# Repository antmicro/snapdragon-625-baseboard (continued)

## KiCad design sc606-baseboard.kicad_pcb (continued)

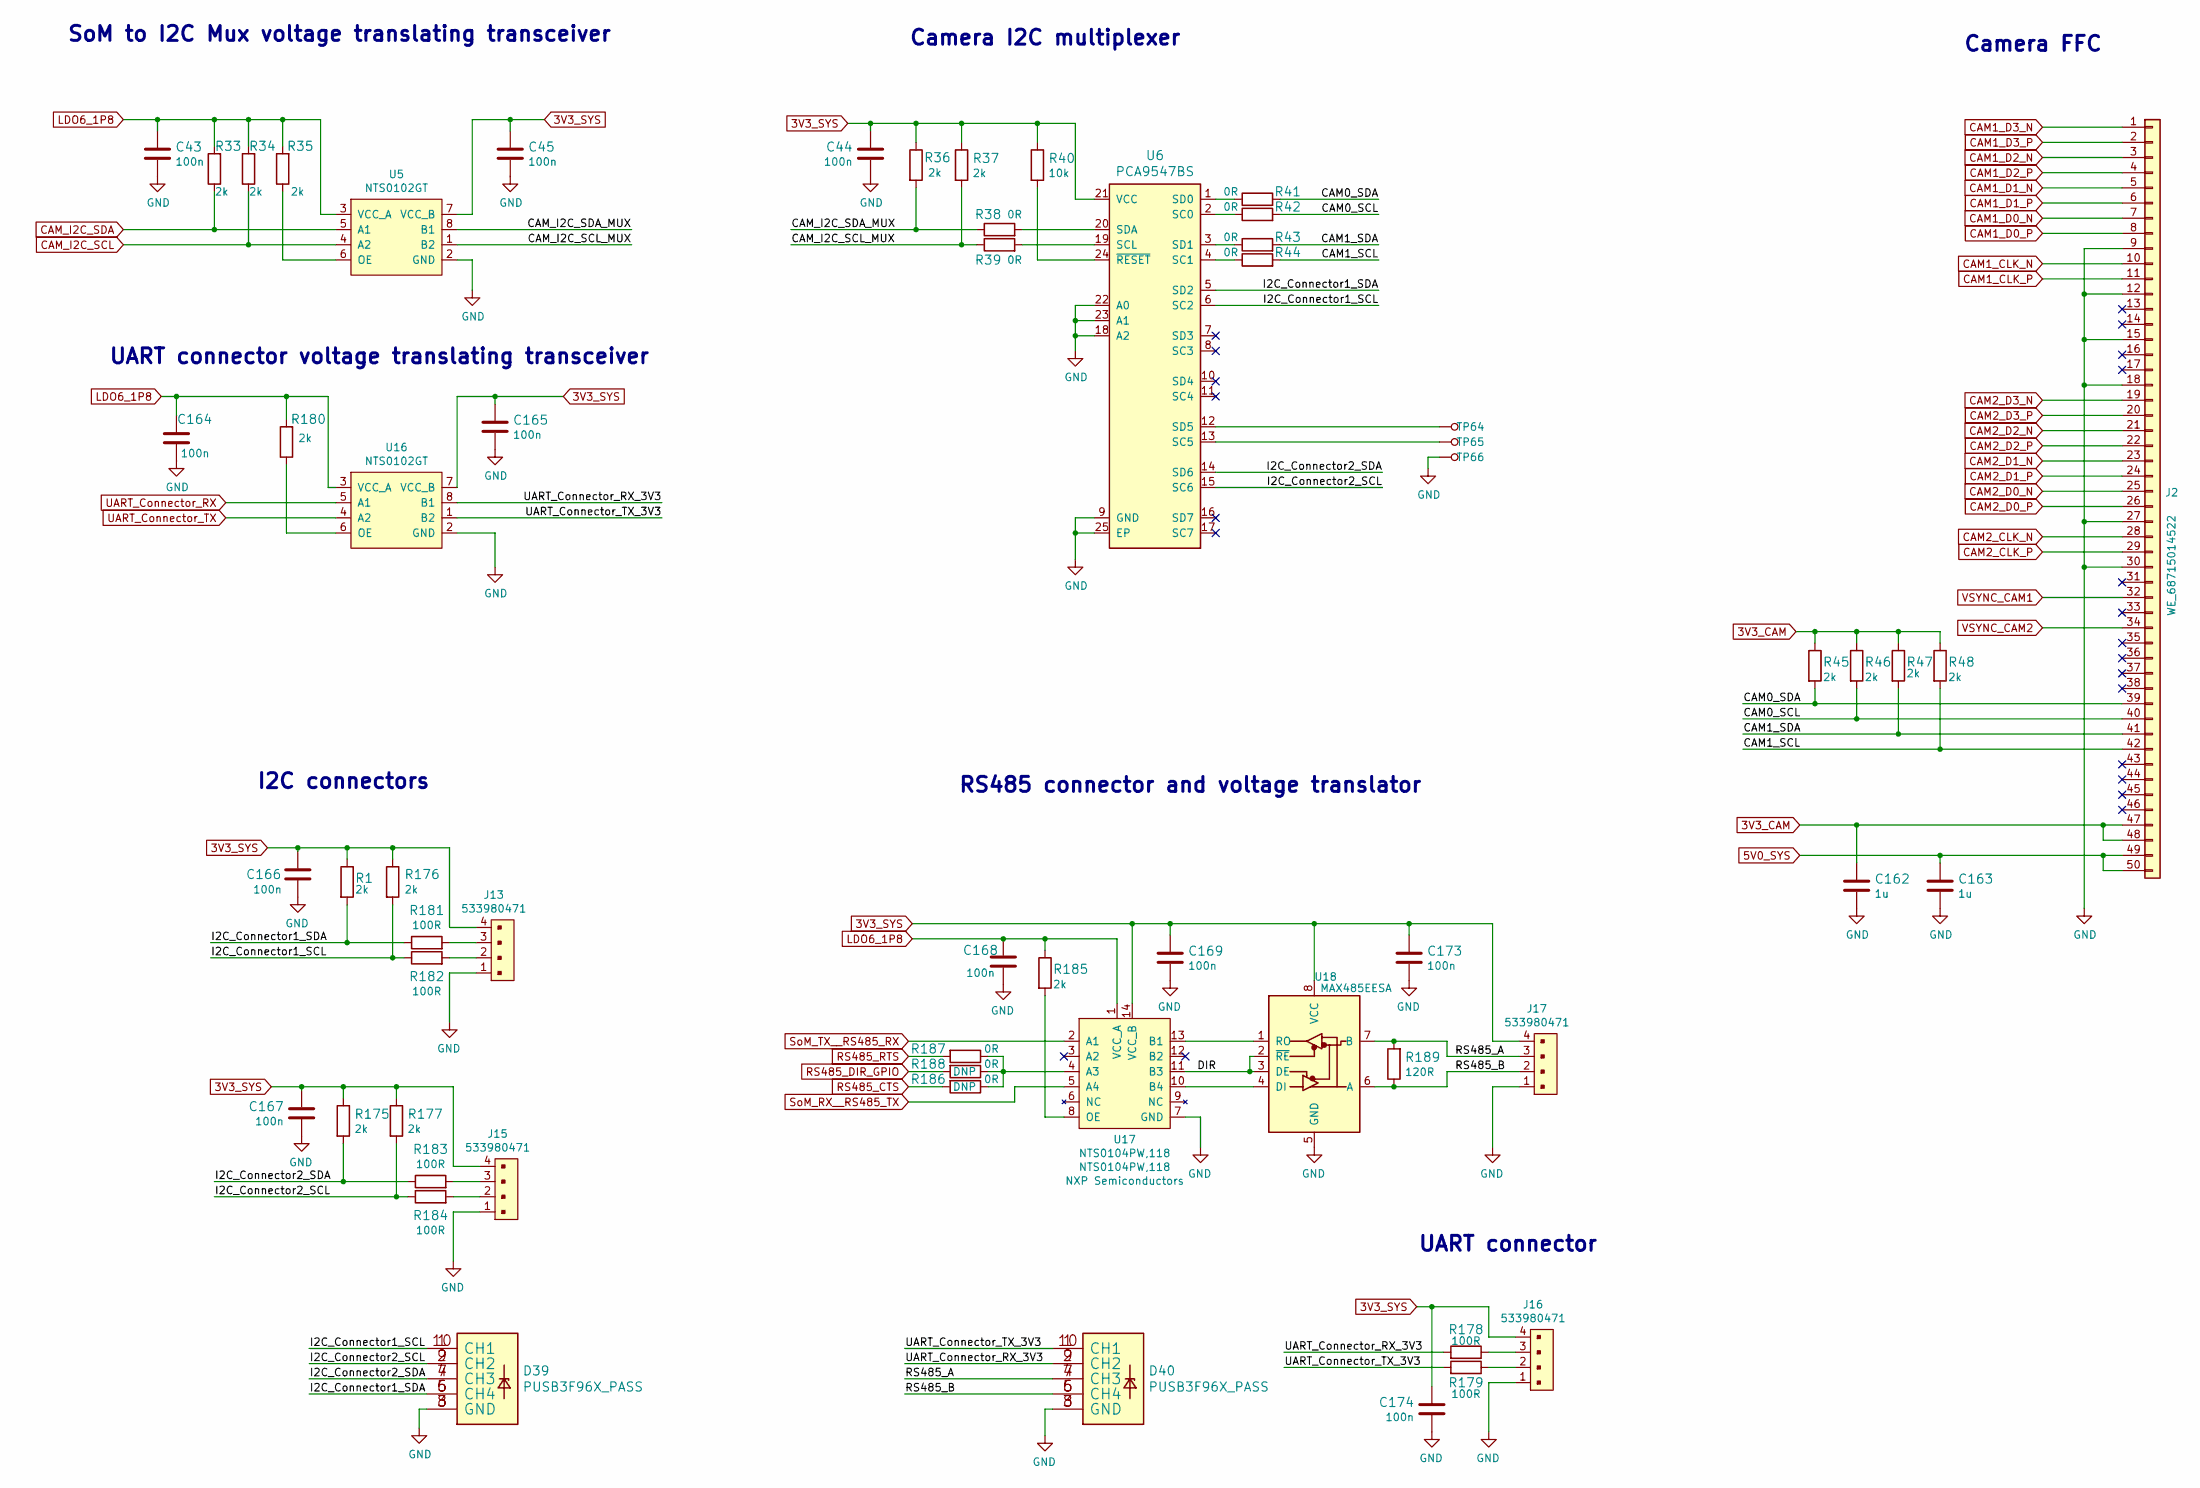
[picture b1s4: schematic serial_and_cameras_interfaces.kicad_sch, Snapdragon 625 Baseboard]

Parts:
C43, C45, C164, C165, C166, C167, C168, C169, C173, C174: C_100n_0402; 0402-cap; MPN GRM155R61H104KE14D
C44: C_100n_0402; 0402-cap; MPN 0402X104K6R3CT
C162, C163: C_1u_0402; 0402-cap; MPN C1005X6S1A105K050BC
D39, D40: PUSB3F96X_PASS; PUSB3F96X; MPN PUSB3F96X
J2: WE_68715014522; MPN 68715014522
J13, J15, J16, J17: 533980471; Molex_PicoBlade_53398-0471_1x04-1MP_P1.25mm_Vertical; MPN 0533980471
R1, R33, R34, R35, R36, R37, R45, R46, R47, R48, R175, R176, R177, R180, R185: R_2k_0402; 0402-res; MPN CRCW04022K00FKED
R38, R39, R41, R42, R43, R44, R186, R187, R188: R_0R_0402; 0402-res; MPN ERJ2GE0R00X
R40: R_10k_0402; 0402-res; MPN CRCW040210K0FKEDHP
R178, R179, R181, R182, R183, R184: R_100R_0402; 0402-res; MPN CR0402-FX-1000GLF
R189: R_120R_0603; 0603-res; MPN CRCW0603120RFKEA
TP64, TP65, TP66: TP_SMD_1_5MM; TP-R-1.5
U5, U16: NTS0102GT; PSON50P100X195X50-8N; MPN NTS0102GT
U6: PCA9547BS; HVQFN24; MPN PCA9547BS,118
U17: NTS0104PW,118; TSSOP-14_W4.4mm; MPN NTS0104PW,118
U18: MAX485EESA; SOIC-8_W3.9mm; MPN MAX485EESA

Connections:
3V3_CAM: C162.1, J2.47, J2.48, R45.1, R46.1, R47.1, R48.1; also elsewhere on the board
3V3_SYS: C44.1, C45.1, C165.1, C166.1, C167.1, C169.1, C173.1, C174.1, J13.4, J15.4, J16.4, J17.4, R1.1, R36.1, R37.1, R40.1, R175.1, R176.1, R177.1, U5.7 (VCC_B), U6.21 (VCC), U16.7 (VCC_B), U17.14 (VCC_B), U18.8 (VCC); also elsewhere on the board
5V0_SYS: C163.1, J2.49, J2.50; also elsewhere on the board
/serial_and_cameras_interfaces/CAM0_SCL: J2.40, R42.2, R46.2
/serial_and_cameras_interfaces/CAM0_SDA: J2.39, R41.2, R45.2
/serial_and_cameras_interfaces/CAM1_SCL: J2.42, R44.2, R48.2
/serial_and_cameras_interfaces/CAM1_SDA: J2.41, R43.2, R47.2
/serial_and_cameras_interfaces/CAM_I2C_SCL_MUX: R37.2, R39.1, U5.1 (B2)
/serial_and_cameras_interfaces/CAM_I2C_SDA_MUX: R36.2, R38.1, U5.8 (B1)
/serial_and_cameras_interfaces/DIR: U17.11 (B3), U18.2 (~RE), U18.3 (DE)
/serial_and_cameras_interfaces/I2C_Connector1_SCL: D39.1 (CH1), D39.10 (CH1), R176.2, R182.1, U6.6 (SC2)
/serial_and_cameras_interfaces/I2C_Connector1_SDA: D39.5 (CH4), D39.6 (CH4), R1.2, R181.1, U6.5 (SD2)
/serial_and_cameras_interfaces/I2C_Connector2_SCL: D39.2 (CH2), D39.9 (CH2), R177.2, R184.1, U6.15 (SC6)
/serial_and_cameras_interfaces/I2C_Connector2_SDA: D39.4 (CH3), D39.7 (CH3), R175.2, R183.1, U6.14 (SD6)
/serial_and_cameras_interfaces/RS485_A: D40.4 (CH3), D40.7 (CH3), J17.3, R189.2, U18.7 (B)
/serial_and_cameras_interfaces/RS485_B: D40.5 (CH4), D40.6 (CH4), J17.2, R189.1, U18.6 (A)
/serial_and_cameras_interfaces/UART_Connector_RX_3V3: D40.2 (CH2), D40.9 (CH2), R178.2, U16.8 (B1)
/serial_and_cameras_interfaces/UART_Connector_TX_3V3: D40.1 (CH1), D40.10 (CH1), R179.2, U16.1 (B2)
CAM1_CLK_N: J2.10; also elsewhere on the board
CAM1_CLK_P: J2.11; also elsewhere on the board
CAM1_D0_N: J2.7; also elsewhere on the board
CAM1_D0_P: J2.8; also elsewhere on the board
CAM1_D1_N: J2.5; also elsewhere on the board
CAM1_D1_P: J2.6; also elsewhere on the board
CAM1_D2_N: J2.3; also elsewhere on the board
CAM1_D2_P: J2.4; also elsewhere on the board
CAM1_D3_N: J2.1; also elsewhere on the board
CAM1_D3_P: J2.2; also elsewhere on the board
CAM2_CLK_N: J2.28; also elsewhere on the board
CAM2_CLK_P: J2.29; also elsewhere on the board
CAM2_D0_N: J2.25; also elsewhere on the board
CAM2_D0_P: J2.26; also elsewhere on the board
CAM2_D1_N: J2.23; also elsewhere on the board
CAM2_D1_P: J2.24; also elsewhere on the board
CAM2_D2_N: J2.21; also elsewhere on the board
CAM2_D2_P: J2.22; also elsewhere on the board
CAM2_D3_N: J2.19; also elsewhere on the board
CAM2_D3_P: J2.20; also elsewhere on the board
CAM_I2C_SCL: R34.1, U5.4 (A2); also elsewhere on the board
CAM_I2C_SDA: R33.1, U5.5 (A1); also elsewhere on the board
GND: C43.2, C44.2, C45.2, C162.2, C163.2, C164.2, C165.2, C166.2, C167.2, C168.2, C169.2, C173.2, C174.2, D39.3 (GND), D39.8 (GND), D40.3 (GND), D40.8 (GND), J2.9, J2.12, J2.15, J2.18, J2.27, J2.30, J13.1, J15.1, J16.1, J17.1, TP66.1, U5.2 (GND), U6.9 (GND), U6.18 (A2), U6.22 (A0), U6.23 (A1), U6.25 (EP), U16.2 (GND), U17.7 (GND), U18.5 (GND); also elsewhere on the board
LDO6_1P8: C43.1, C164.1, C168.1, R33.2, R34.2, R35.2, R180.2, R185.1, U5.3 (VCC_A), U16.3 (VCC_A), U17.1 (VCC_A); also elsewhere on the board
unnamed: J13.2, R182.2
unnamed: J13.3, R181.2
unnamed: J15.2, R184.2
unnamed: J15.3, R183.2
unnamed: J16.2, R179.1
unnamed: J16.3, R178.1
unnamed: R35.1, U5.6 (OE)
unnamed: R38.2, U6.20 (SDA)
unnamed: R39.2, U6.19 (SCL)
unnamed: R40.2, U6.24 (~RESET)
unnamed: R41.1, U6.1 (SD0)
unnamed: R42.1, U6.2 (SC0)
unnamed: R43.1, U6.3 (SD1)
unnamed: R44.1, U6.4 (SC1)
unnamed: R180.1, U16.6 (OE)
unnamed: R185.2, U17.8 (OE)
unnamed: R186.1, R187.1, R188.1, U17.4 (A3)
unnamed: TP64.1, U6.12 (SD5)
unnamed: TP65.1, U6.13 (SC5)
unnamed: U17.10 (B4), U18.4 (DI)
unnamed: U17.13 (B1), U18.1 (RO)
RS485_CTS: R186.2; also elsewhere on the board
RS485_DIR_GPIO: R188.2; also elsewhere on the board
RS485_RTS: R187.2; also elsewhere on the board
SoM_RX__RS485_TX: U17.5 (A4); also elsewhere on the board
SoM_TX__RS485_RX: U17.2 (A1); also elsewhere on the board
UART_Connector_RX: U16.5 (A1); also elsewhere on the board
UART_Connector_TX: U16.4 (A2); also elsewhere on the board
VSYNC_CAM1: J2.32; also elsewhere on the board
VSYNC_CAM2: J2.34; also elsewhere on the board

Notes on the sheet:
UART connector
UART connector voltage translating transceiver
RS485 connector and voltage translator
SoM to I2C Mux voltage translating transceiver
Camera I2C multiplexer
Camera FFC
I2C connectors

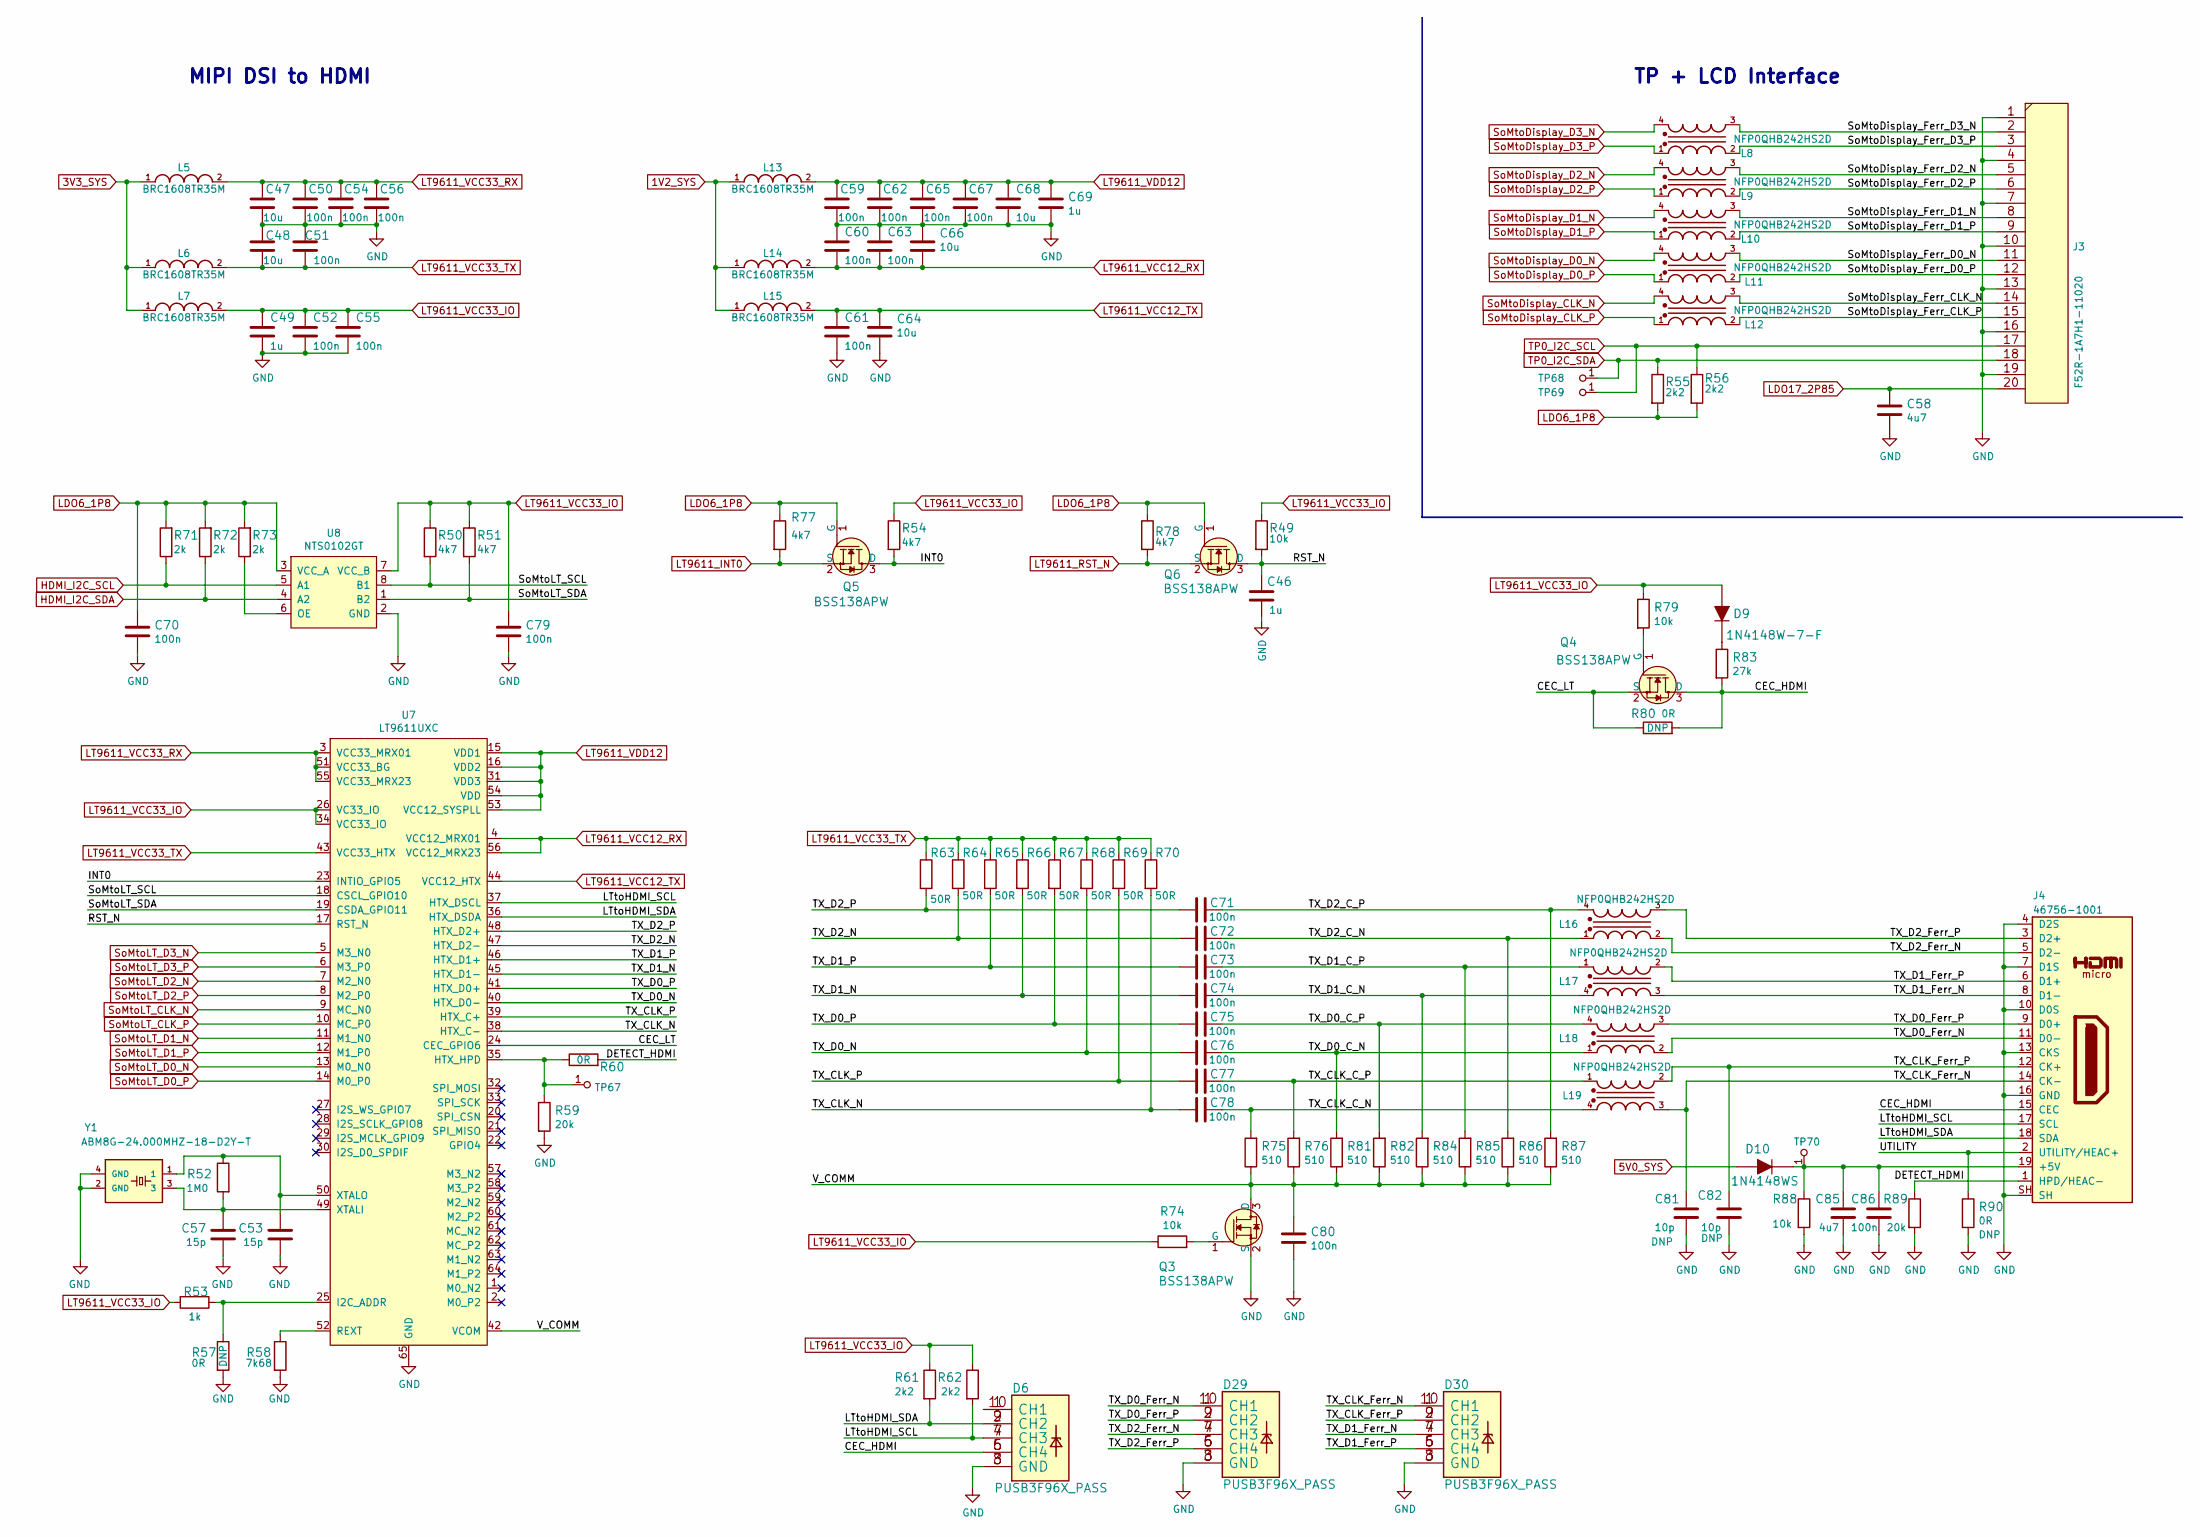
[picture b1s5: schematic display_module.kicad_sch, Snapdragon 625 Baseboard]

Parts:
C46, C49, C69: C_1u_0402; 0402-cap; MPN C1005X6S1A105K050BC
C47, C48, C64, C66, C68: C_10u_0402; 0402-cap; MPN CC0402MRX5R5BB106
C50, C51, C52, C54, C55, C56, C59, C60, C61, C62, C63, C65, C67, C70, C71, C72, C73, C74, C75, C76, C77, C78, C79, C80, C86: C_100n_0402; 0402-cap; MPN GRM155R61H104KE14D
C53, C57: C_15p_0402; 0402-cap; MPN MC0402N150J500CT
C58, C85: C_4u7_0402; 0402-cap; MPN GRM155R61A475MEAAD
C81, C82: C_10p_0402; 0402-cap; MPN MC0402N100D500CT
D6, D29, D30: PUSB3F96X_PASS; PUSB3F96X; MPN PUSB3F96X
D9: 1N4148W-7-F; SOD-123; MPN 1N4148W-7-F
D10: 1N4148WS; SOD-323F; MPN 1N4148WS
J3: F52R-1A7H1-11020; MPN F52R-1A7H1-11020
J4: 46756-1001; HDMI_Micro-D_Molex_46765-1x01; MPN 467651001
L5, L6, L7, L13, L14, L15: BRC1608TR35M; INDC1608X100N; MPN BRC1608TR35M
L8, L9, L10, L11, L12, L16, L17, L18, L19: NFP0QHB242HS2D; FIL_NFP0QHB242HS2D; MPN NFP0QHB242HS2D
Q3, Q4, Q5, Q6: BSS138APW; SC70-3; MPN BSS138PW
R49, R74, R79, R88: R_10k_0402; 0402-res; MPN CRCW040210K0FKEDHP
R50, R51, R54, R77, R78: R_4k7_0402; 0402-res; MPN MCS04020C4701FE000
R52: R_1M0_0402; 0402-res; MPN CRG0402F1M0
R53: R_1k_0402; 0402-res; MPN CR0402-FX-1001GLF
R55, R56, R61, R62: R_2k2_0402; 0402-res; MPN RC0402FR-072K2L
R57, R60, R80, R90: R_0R_0402; 0402-res; MPN ERJ2GE0R00X
R58: R_7k68_0603; 0603-res; MPN WR06X7681FTL
R59, R89: R_20k_0402; 0402-res; MPN CRCW040220K0FKED
R63, R64, R65, R66, R67, R68, R69, R70: R_50R_0402; 0402-res; MPN RN73R1ETTP50R0F50
R71, R72, R73: R_2k_0402; 0402-res; MPN CRCW04022K00FKED
R75, R76, R81, R82, R84, R85, R86, R87: R_510_0402; 0402-res; MPN CRCW0402510RFKEDC
R83: R_27k_0402; 0402-res; MPN ERJ2RKF2702X
TP67, TP68, TP69, TP70: TP; TP-R-1.5
U7: LT9611UXC; LT9611; MPN LT9611
U8: NTS0102GT; PSON50P100X195X50-8N; MPN NTS0102GT
Y1: ABM8G-24.000MHZ-18-D2Y-T; KX-7; MPN ABM8G-24.000MHZ-18-D2Y-T

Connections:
1V2_SYS: L13.1, L14.1, L15.1; also elsewhere on the board
3V3_SYS: L5.1, L6.1, L7.1; also elsewhere on the board
5V0_SYS: D10.A; also elsewhere on the board
/display module/CEC_HDMI: D6.5 (CH4), D6.6 (CH4), J4.15 (CEC), Q4.3 (D), R80.2, R83.2
/display module/CEC_LT: Q4.2 (S), R80.1, U7.24 (CEC_GPIO6)
/display module/DETECT_HDMI: J4.1 (HPD/HEAC-), R60.2, R89.1
/display module/INT0: Q5.3 (D), R54.2, U7.23 (INTIO_GPIO5)
/display module/LTtoHDMI_SCL: D6.4 (CH3), D6.7 (CH3), J4.17 (SCL), R62.2, U7.37 (HTX_DSCL)
/display module/LTtoHDMI_SDA: D6.2 (CH2), D6.9 (CH2), J4.18 (SDA), R61.2, U7.36 (HTX_DSDA)
/display module/RST_N: C46.1, Q6.3 (D), R49.2, U7.17 (RST_N)
/display module/SoMtoDisplay_Ferr_CLK_N: J3.14, L12.3
/display module/SoMtoDisplay_Ferr_CLK_P: J3.15, L12.2
/display module/SoMtoDisplay_Ferr_D0_N: J3.11, L11.3
/display module/SoMtoDisplay_Ferr_D0_P: J3.12, L11.2
/display module/SoMtoDisplay_Ferr_D1_N: J3.8, L10.3
/display module/SoMtoDisplay_Ferr_D1_P: J3.9, L10.2
/display module/SoMtoDisplay_Ferr_D2_N: J3.5, L9.3
/display module/SoMtoDisplay_Ferr_D2_P: J3.6, L9.2
/display module/SoMtoDisplay_Ferr_D3_N: J3.2, L8.3
/display module/SoMtoDisplay_Ferr_D3_P: J3.3, L8.2
/display module/SoMtoLT_SCL: R50.2, U7.18 (CSCL_GPIO10), U8.8 (B1)
/display module/SoMtoLT_SDA: R51.2, U7.19 (CSDA_GPIO11), U8.1 (B2)
/display module/TX_CLK_C_N: C78.1, L19.4, R75.2
/display module/TX_CLK_C_P: C77.1, L19.1, R76.2
/display module/TX_CLK_Ferr_N: C81.1, D30.1 (CH1), D30.10 (CH1), J4.14 (CK-), L19.3
/display module/TX_CLK_Ferr_P: C82.1, D30.2 (CH2), D30.9 (CH2), J4.12 (CK+), L19.2
/display module/TX_CLK_N: C78.2, R70.2, U7.38 (HTX_C-)
/display module/TX_CLK_P: C77.2, R69.2, U7.39 (HTX_C+)
/display module/TX_D0_C_N: C76.1, L18.1, R81.2
/display module/TX_D0_C_P: C75.1, L18.4, R82.2
/display module/TX_D0_Ferr_N: D29.1 (CH1), D29.10 (CH1), J4.11 (D0-), L18.2
/display module/TX_D0_Ferr_P: D29.2 (CH2), D29.9 (CH2), J4.9 (D0+), L18.3
/display module/TX_D0_N: C76.2, R68.2, U7.40 (HTX_D0-)
/display module/TX_D0_P: C75.2, R67.2, U7.41 (HTX_D0+)
/display module/TX_D1_C_N: C74.1, L17.4, R84.2
/display module/TX_D1_C_P: C73.1, L17.1, R85.2
/display module/TX_D1_Ferr_N: D30.4 (CH3), D30.7 (CH3), J4.8 (D1-), L17.3
/display module/TX_D1_Ferr_P: D30.5 (CH4), D30.6 (CH4), J4.6 (D1+), L17.2
/display module/TX_D1_N: C74.2, R66.2, U7.45 (HTX_D1-)
/display module/TX_D1_P: C73.2, R65.2, U7.46 (HTX_D1+)
/display module/TX_D2_C_N: C72.1, L16.1, R86.2
/display module/TX_D2_C_P: C71.1, L16.4, R87.2
/display module/TX_D2_Ferr_N: D29.4 (CH3), D29.7 (CH3), J4.5 (D2-), L16.2
/display module/TX_D2_Ferr_P: D29.5 (CH4), D29.6 (CH4), J4.3 (D2+), L16.3
/display module/TX_D2_N: C72.2, R64.2, U7.47 (HTX_D2-)
/display module/TX_D2_P: C71.2, R63.2, U7.48 (HTX_D2+)
/display module/UTILITY: J4.2 (UTILITY/HEAC+), R90.1
/display module/V_COMM: C80.1, Q3.3 (D), R75.1, R76.1, R81.1, R82.1, R84.1, R85.1, R86.1, R87.1, U7.42 (VCOM)
GND: C46.2, C47.1, C48.2, C49.2, C50.1, C51.2, C52.2, C53.2, C54.1, C55.2, C56.1, C57.2, C58.2, C59.1, C60.1, C61.2, C62.1, C63.1, C64.2, C65.1, C66.1, C67.1, C68.2, C69.2, C70.2, C79.2, C80.2, C81.2, C82.2, C85.2, C86.2, D6.3 (GND), D6.8 (GND), D29.3 (GND), D29.8 (GND), D30.3 (GND), D30.8 (GND), J3.1, J3.4, J3.7, J3.10, J3.13, J3.16, J3.19, J4.4 (D2S), J4.7 (D1S), J4.10 (D0S), J4.13 (CKS), J4.16 (GND), J4.SH, Q3.2 (S), R57.2, R58.2, R59.2, R88.2, R89.2, R90.2, U7.65 (GND), U8.2 (GND), Y1.2 (GND), Y1.4 (GND); also elsewhere on the board
HDMI_I2C_SCL: R71.1, U8.5 (A1); also elsewhere on the board
HDMI_I2C_SDA: R72.1, U8.4 (A2); also elsewhere on the board
LDO6_1P8: C70.1, Q5.1 (G), Q6.1 (G), R55.2, R56.2, R71.2, R72.2, R73.2, R77.1, R78.1, U8.3 (VCC_A); also elsewhere on the board
LDO17_2P85: C58.1, J3.20; also elsewhere on the board
LT9611_INT0: Q5.2 (S), R77.2; also elsewhere on the board
LT9611_RST_N: Q6.2 (S), R78.2; also elsewhere on the board
LT9611_VCC12_RX: C60.2, C63.2, C66.2, L14.2, U7.4 (VCC12_MRX01), U7.56 (VCC12_MRX23)
LT9611_VCC12_TX: C61.1, C64.1, L15.2, U7.44 (VCC12_HTX)
LT9611_VCC33_IO: C49.1, C52.1, C55.1, C79.1, D9.A, L7.2, R49.1, R50.1, R51.1, R53.2, R54.1, R61.1, R62.1, R74.1, R79.1, U7.26 (VC33_IO), U7.34 (VCC33_IO), U8.7 (VCC_B)
LT9611_VCC33_RX: C47.2, C50.2, C54.2, C56.2, L5.2, U7.3 (VCC33_MRX01), U7.51 (VCC33_BG), U7.55 (VCC33_MRX23)
LT9611_VCC33_TX: C48.1, C51.1, L6.2, R63.1, R64.1, R65.1, R66.1, R67.1, R68.1, R69.1, R70.1, U7.43 (VCC33_HTX)
LT9611_VDD12: C59.2, C62.2, C65.2, C67.2, C68.1, C69.1, L13.2, U7.15 (VDD1), U7.16 (VDD2), U7.31 (VDD3), U7.53 (VCC12_SYSPLL), U7.54 (VDD)
unnamed: C53.1, R52.1, U7.50 (XTALO), Y1.1
unnamed: C57.1, R52.2, U7.49 (XTALI), Y1.3
unnamed: C85.1, C86.1, D10.K, J4.19 (+5V), R88.1, TP70.1
unnamed: D6.1 (CH1), D6.10 (CH1)
unnamed: D9.K, R83.1
unnamed: Q3.1 (G), R74.2
unnamed: Q4.1 (G), R79.2
unnamed: R53.1, R57.1, U7.25 (I2C_ADDR)
unnamed: R58.1, U7.52 (REXT)
unnamed: R59.1, R60.1, TP67.1, U7.35 (HTX_HPD)
unnamed: R73.1, U8.6 (OE)
SoMtoDisplay_CLK_N: L12.4; also elsewhere on the board
SoMtoDisplay_CLK_P: L12.1; also elsewhere on the board
SoMtoDisplay_D0_N: L11.4; also elsewhere on the board
SoMtoDisplay_D0_P: L11.1; also elsewhere on the board
SoMtoDisplay_D1_N: L10.4; also elsewhere on the board
SoMtoDisplay_D1_P: L10.1; also elsewhere on the board
SoMtoDisplay_D2_N: L9.4; also elsewhere on the board
SoMtoDisplay_D2_P: L9.1; also elsewhere on the board
SoMtoDisplay_D3_N: L8.4; also elsewhere on the board
SoMtoDisplay_D3_P: L8.1; also elsewhere on the board
SoMtoLT_CLK_N: U7.9 (MC_N0); also elsewhere on the board
SoMtoLT_CLK_P: U7.10 (MC_P0); also elsewhere on the board
SoMtoLT_D0_N: U7.13 (M0_N0); also elsewhere on the board
SoMtoLT_D0_P: U7.14 (M0_P0); also elsewhere on the board
SoMtoLT_D1_N: U7.11 (M1_N0); also elsewhere on the board
SoMtoLT_D1_P: U7.12 (M1_P0); also elsewhere on the board
SoMtoLT_D2_N: U7.7 (M2_N0); also elsewhere on the board
SoMtoLT_D2_P: U7.8 (M2_P0); also elsewhere on the board
SoMtoLT_D3_N: U7.5 (M3_N0); also elsewhere on the board
SoMtoLT_D3_P: U7.6 (M3_P0); also elsewhere on the board
TP0_I2C_SCL: J3.17, R56.1, TP69.1; also elsewhere on the board
TP0_I2C_SDA: J3.18, R55.1, TP68.1; also elsewhere on the board

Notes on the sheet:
MIPI DSI to HDMI
TP + LCD Interface

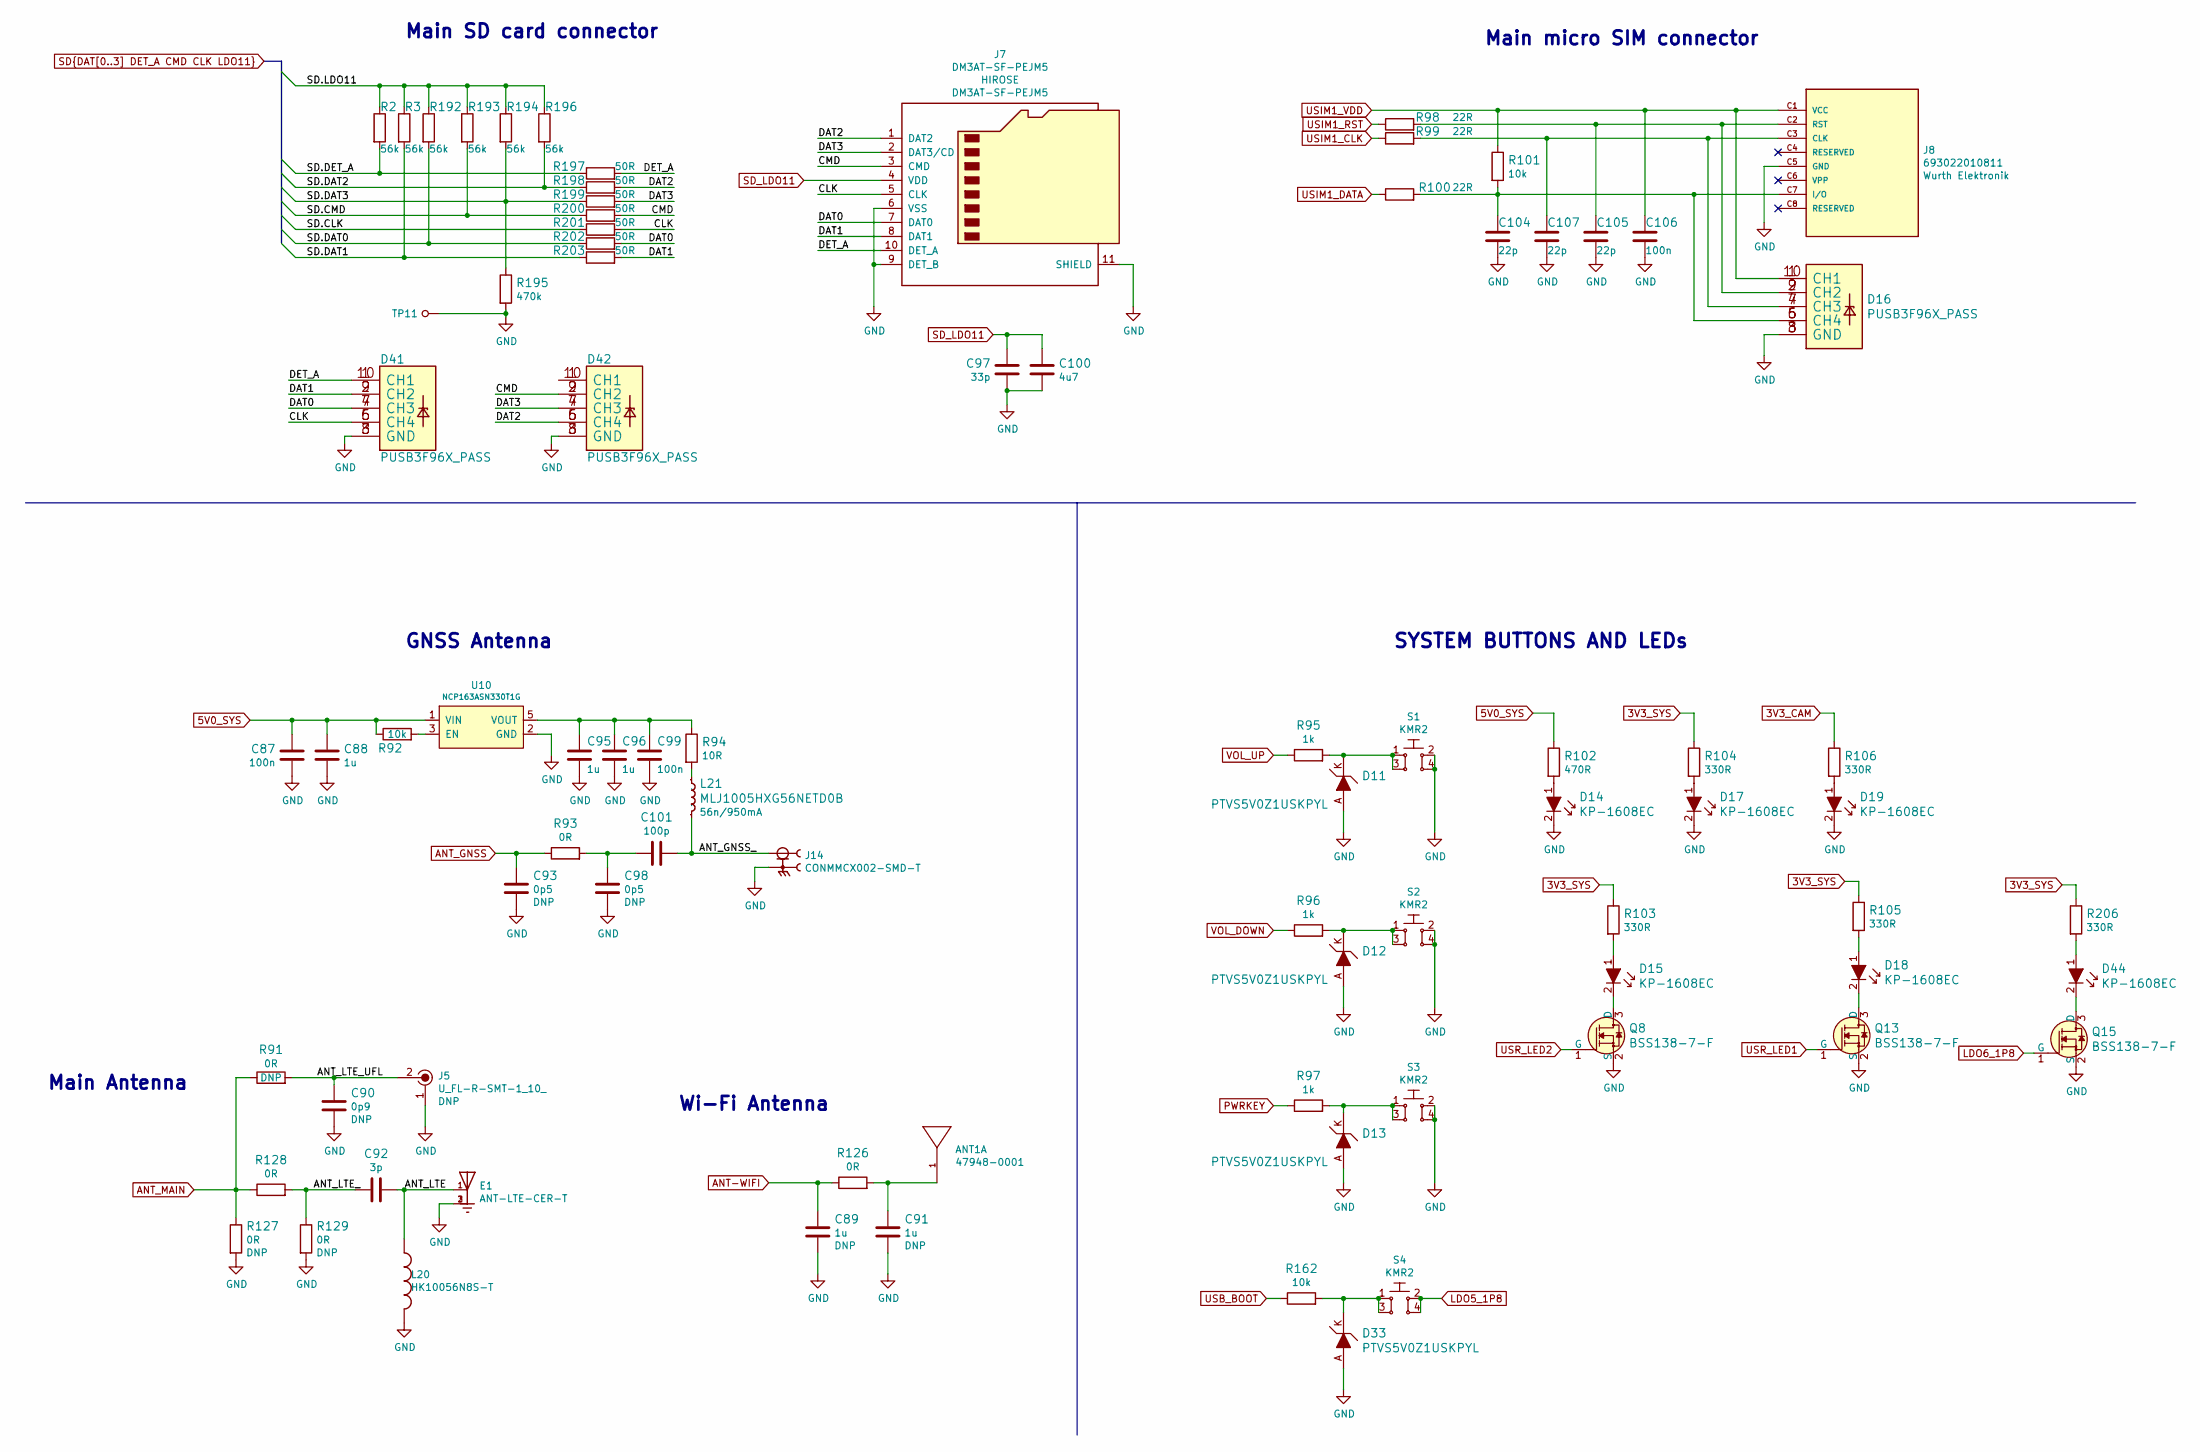
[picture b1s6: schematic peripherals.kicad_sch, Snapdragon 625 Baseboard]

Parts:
ANT1: 47948-0001; MPN 47948-0001
C87, C99: C_100n_0402; 0402-cap; MPN GRM155R61H104KE14D
C88, C89, C91, C95, C96: C_1u_0402; 0402-cap; MPN C1005X6S1A105K050BC
C90: C_0p9_0402; 0402-cap; MPN GJM1555C1HR90DB01D
C92: C_3p_0402; 0402-cap; MPN MC0402N3R0C500CT
C93, C98: C_0p5_0402; 0402-cap; MPN GJM1555C1HR50WB01D
C97: C_33p_0402; 0402-cap; MPN MC0402N330J500CT
C100: C_4u7_0402; 0402-cap; MPN GRM155R61A475MEAAD
C101: C_100p_0402; 0402-cap; MPN 0402N101J500CT
C104, C105, C107: C_22p_0402; 0402-cap; MPN CC0402JRNPO9BN220
C106: C_100n_0402; 0402-cap; MPN 0402X104K6R3CT
D11, D12, D13, D33: PTVS5V0Z1USKPYL; SOD-964; MPN PTVS5V0Z1USKPYL
D14, D15, D17, D18, D19, D44: KP-1608EC; LED_0603; MPN KP-1608EC
D16, D41, D42: PUSB3F96X_PASS; PUSB3F96X; MPN PUSB3F96X
E1: ANT-LTE-CER-T; XDCR_ANT-LTE-CER-T; MPN ANT-LTE-CER-T
J5: U_FL-R-SMT-1_10_; Coax_Conn_U.FL; MPN U.FL-R-SMT-1(10)
J7: DM3AT-SF-PEJM5; MicroSD_DM3AT-SF-PEJM5; MPN DM3AT-SF-PEJM5
J8: 693022010811; MPN 693022010811
J14: CONMMCX002-SMD-T; LINX_CONMMCX002-SMD-T; MPN CONMMCX002-SMD-T
L20: HK10056N8S-T; INDC1005X55N; MPN HK10056N8S-T
L21: MLJ1005HXG56NETD0B; 0402-res; MPN MLJ1005HXG56NETD0B
Q8, Q13, Q15: BSS138-7-F; SOT-23-3; MPN BSS138-7-F
R2, R3, R192, R193, R194, R196: R_56k_0402; 0402-res; MPN CRCW040256K0FKED
R91, R93, R126, R127, R128, R129: R_0R_0402; 0402-res; MPN ERJ2GE0R00X
R92, R101, R162: R_10k_0402; 0402-res; MPN CRCW040210K0FKEDHP
R94: R_10R_0603; 0603-res; MPN MCWR06X10R0FTL
R95, R96, R97: R_1k_0402; 0402-res; MPN CR0402-FX-1001GLF
R98, R99, R100: R_22R_0402; 0402-res; MPN CRCW040222R0FKED
R102: R_470R_0402; 0402-res; MPN CRCW0402470RFKED
R103, R104, R105, R106, R206: R_330R_0402; 0402-res; MPN MCMR04X3300FTL
R195: R_470k_0402; 0402-res; MPN RC0402FR-07470KL
R197, R198, R199, R200, R201, R202, R203: R_50R_0402; 0402-res; MPN RN73R1ETTP50R0F50
S1, S2, S3, S4: KMR2; SW_SPST_4.2x2.8; MPN KMR211NGLFS
TP11: TP_SMD_1_5MM; TP-R-1.5
U10: NCP163ASN330T1G; SOT-23-5; MPN NCP163ASN330T1G

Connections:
3V3_CAM: R106.1; also elsewhere on the board
3V3_SYS: R103.1, R104.1, R105.1, R206.1; also elsewhere on the board
5V0_SYS: C87.1, C88.1, R92.1, R102.1, U10.1 (VIN); also elsewhere on the board
/peripherals/ANT_GNSS_: C101.1, J14.1, L21.2
/peripherals/ANT_LTE: C92.1, E1.1, L20.1
/peripherals/ANT_LTE_: C92.2, R128.2, R129.1
/peripherals/ANT_LTE_UFL: C90.1, J5.2, R91.2
/peripherals/CLK: D41.5 (CH4), D41.6 (CH4), J7.5 (CLK), R201.2
/peripherals/CMD: D42.2 (CH2), D42.9 (CH2), J7.3 (CMD), R200.2
/peripherals/DAT0: D41.4 (CH3), D41.7 (CH3), J7.7 (DAT0), R202.2
/peripherals/DAT1: D41.2 (CH2), D41.9 (CH2), J7.8 (DAT1), R203.2
/peripherals/DAT2: D42.5 (CH4), D42.6 (CH4), J7.1 (DAT2), R198.2
/peripherals/DAT3: D42.4 (CH3), D42.7 (CH3), J7.2 (DAT3/CD), R199.2
/peripherals/DET_A: D41.1 (CH1), D41.10 (CH1), J7.10 (DET_A), R197.2
ANT-WIFI: C89.1, R126.1; also elsewhere on the board
ANT_GNSS: C93.1, R93.1; also elsewhere on the board
ANT_MAIN: R91.1, R127.1, R128.1; also elsewhere on the board
GND: C87.2, C88.2, C89.2, C90.2, C91.2, C93.2, C95.2, C96.2, C97.2, C98.2, C99.2, C100.2, C104.2, C105.2, C106.2, C107.2, D11.A, D12.A, D13.A, D14.2, D16.3 (GND), D16.8 (GND), D17.2, D19.2, D33.A, D41.3 (GND), D41.8 (GND), D42.3 (GND), D42.8 (GND), E1.2, E1.3, J5.1, J7.6 (VSS), J7.9 (DET_B), J7.11 (SHIELD), J8.C5 (GND), J8.Z1 (GND), J8.Z2 (GND), J14.S1, J14.S2, J14.S3, J14.S4, L20.2, Q8.2 (S), Q13.2 (S), Q15.2 (S), R127.2, R129.2, R195.2, S1.2, S1.4, S2.2, S2.4, S3.2, S3.4, TP11.1, U10.2 (GND); also elsewhere on the board
LDO5_1P8: S4.2, S4.4; also elsewhere on the board
LDO6_1P8: Q15.1 (G); also elsewhere on the board
unnamed: ANT1.1 (FEEDING_PAD), C91.1, R126.2
unnamed: C95.1, C96.1, C99.1, R94.1, U10.5 (VOUT)
unnamed: C98.1, C101.2, R93.2
unnamed: C104.1, D16.5 (CH4), D16.6 (CH4), J8.C7 (I/O), R100.2, R101.2
unnamed: C105.1, D16.2 (CH2), D16.9 (CH2), J8.C2 (RST), R98.2
unnamed: C107.1, D16.4 (CH3), D16.7 (CH3), J8.C3 (CLK), R99.2
unnamed: D11.K, R95.2, S1.1, S1.3
unnamed: D12.K, R96.2, S2.1, S2.3
unnamed: D13.K, R97.2, S3.1, S3.3
unnamed: D14.1, R102.2
unnamed: D15.1, R103.2
unnamed: D15.2, Q8.3 (D)
unnamed: D17.1, R104.2
unnamed: D18.1, R105.2
unnamed: D18.2, Q13.3 (D)
unnamed: D19.1, R106.2
unnamed: D33.K, R162.2, S4.1, S4.3
unnamed: D42.1 (CH1), D42.10 (CH1)
unnamed: D44.1, R206.2
unnamed: D44.2, Q15.3 (D)
unnamed: L21.1, R94.2
unnamed: R92.2, U10.3 (EN)
PWRKEY: R97.1; also elsewhere on the board
SD_DATA_0: R192.2, R202.1; also elsewhere on the board
SD_DATA_1: R3.2, R203.1; also elsewhere on the board
SD_DATA_2: R196.2, R198.1; also elsewhere on the board
SD_DATA_3: R194.2, R195.1, R199.1; also elsewhere on the board
SD_DATA_4: R201.1; also elsewhere on the board
SD_DATA_5: R193.2, R200.1; also elsewhere on the board
SD_DATA_6: R2.2, R197.1; also elsewhere on the board
USB_BOOT: R162.1; also elsewhere on the board
USIM1_CLK: R99.1; also elsewhere on the board
USIM1_DATA: R100.1; also elsewhere on the board
USIM1_RST: R98.1; also elsewhere on the board
USIM1_VDD: C106.1, D16.1 (CH1), D16.10 (CH1), J8.C1 (VCC), R101.1; also elsewhere on the board
USR_LED1: Q13.1 (G); also elsewhere on the board
USR_LED2: Q8.1 (G); also elsewhere on the board
VOL_DOWN: R96.1; also elsewhere on the board
VOL_UP: R95.1; also elsewhere on the board

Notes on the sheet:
Main micro SIM connector
GNSS Antenna
Main Antenna
Main SD card connector
Wi-Fi Antenna
SYSTEM BUTTONS AND LEDs
